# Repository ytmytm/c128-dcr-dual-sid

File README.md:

# Dual SID for C128DCR and C128D

This is a daughterboard that allows to have dual SID audio in a C128DCR. Although C128DCR has a huge case the space near SID and MMU is very awkward due to power supply.

This project is meant for two 8580 chips, as far as I know the only type installed in C128DCRs. But you never know, so just in case I left information about supporting 6581 SIDs too.

## Background

The goal of this project was to make the PCB fit in the narrow area between power supply and already installed
[256K MMU expansion](https://github.com/ytmytm/c128-mmu-256k-exp).

The audio output is mixed as 6-voices mono and passed through onboard amplifier to audio/video port.

The board supports various modes for external input, including noise reduction and digi boost.

## Design

This is basically a fusion of ideas from two projects:

- [C64 Stereo SID](https://github.com/tebl/C64-Stereo-SID) by tebl (seed project for schematic and PCB)
- [MixSID](http://henning-liebenau.de/mixsid/) by Henning Bekel (noise reduction and digi boost)

I have mostly done measurements and shaped the PCB.

### Schematic

PDF plot of [the schematic can be found here](kicad/plots/C128DCR%20Dual%20SID.pdf).

[kicad](kicad/) folder contains all the KiCad 6.0 project files for C128DCR.

[kicad-c128d](kicad-c128d/) folder contains all the KiCad 6.0 project files for C128D.

### PCB

[kicad/plots](kicad/plots) folder contains Gerber files for manufacturing a PCB.

The PCB hugs 256K MMU expansion board on one side, tries to avoid power supply on the other side and also has to leave space for screw standoff under the power supply module.

[kicad-c128d/plots](kicad-c128d/plots) folder contains all the KiCad 6.0 project files for C128D.

## PCB Assembly

Both SID chips must be identical. For C128DCR these should be usually MOS 8580 powered by 9V.

For 8580:

- be sure that the voltage between pins 14 (GND) and 28 (VDD) of SID socket is 9V
- do not install resistor R8
- use 22nF (symbol 223) capacitors for C71/C72

For 6581:

- be sure that the voltage between pins 14 (GND) and 28 (VDD) of SID socket is 12V
- install resistor R8
- use 470pF (symbol 471) capacitors for C71/C72

## Jumpers

Jumpers JP1/JP3 (SID#1) and JP2/JP4 (SID#2) control external input/noise reduction/digi boost signal routing.

JP1 and JP2 (square pad is pin 1):

- short 1-2 for noise reduction
- short 2-3 to pass external input from audio/video port

JP3 and JP4 (square pad is pin 1):

- short 1-2 to choose signal selected by JP1/JP2: external input or noise reduction
- short 2-3 to enable digi boost instead, this is meant for 8580

You can also keep all jumpers open to make external input floating. Some people claim that it's another way of reducing the noise.

For digi boost additionally set RV1 and RV2 trimmers while playing some sampled audio to bring digital sound to an acceptable volume level relative to regular SID voices.

[MixSID configuration tool](http://henning-liebenau.de/mixsid/configurator.html) has excellent description of both noise reduction and digi boost modes.

On the image above there is a single ARMSID as primary SID and an unpopulated socket for secondary SID.

For both chips the board is configured with JP3/JP4 for digi boost, so JP1/JP2 set to noise reduction are irrelevant.

Note that R8 is installed here by mistake, but its one leg was cut.

## Installation tips

### C128DCR

- solder round pins to two rows of the `SID_ADAPTER` footprint first.
- then solder lowest components first: the resistors (skip R8 if you are going to use 8580 chips)
- then two sockets for primary and secondary SIDs, check the orientation
- finally capacitors and trimmers; pay attention to the correct C70/C71 values

There are small holes in the PCB where plastic standoffs can be put to support the board on both ends and reduce stress on the mainboard SID socket.
It's especially important on the top right end, next to secondary SID.

After assembling two such boards I noticed that power supply modules in different C128DCRs have different dimensions.
To be sure that nothing will be shorted I put kapton tape on the whole left-hand side of the board after installation, also covering socketed primary SID.

### C128D

Start by soldering round pins to row closest to the PCB's edge and to the row marked on the silkscreen. Then proceed with C128DCR instructions.

## SID#2 chip select signal and testing

You need to decide where in the I/O memory space SID#2 will be available.
Even though signal for $D700 is easily available on C128 (it's pin 12 of U3) most stereo/dual SID tunes use $D420, $D500 or $DE00.

For quick tests SID#2 chip select signal (`/CS2_IN`, the square pad on J4 connector) can come from `I/O1` signal to make SID#2 appear at $DE00 address.
You don't need to reach to expansion port for that, it's already available on pin 9 of U3. Obviously it's not compatible with cartridges but allows for a quick test.

Download this tune: https://csdb.dk/release/?id=96893 and run. Hit '3' to choose $DE00 and you should hear the music - it starts immediately playing on SID#2 channels, SID#1 joins later - after about 30s.

Check out [my other project](https://github.com/ytmytm/c128-u3-replacement) for a better solution to make SID#2 appear at $D420, $D500 (in C64 mode) and optionally at $DE00.

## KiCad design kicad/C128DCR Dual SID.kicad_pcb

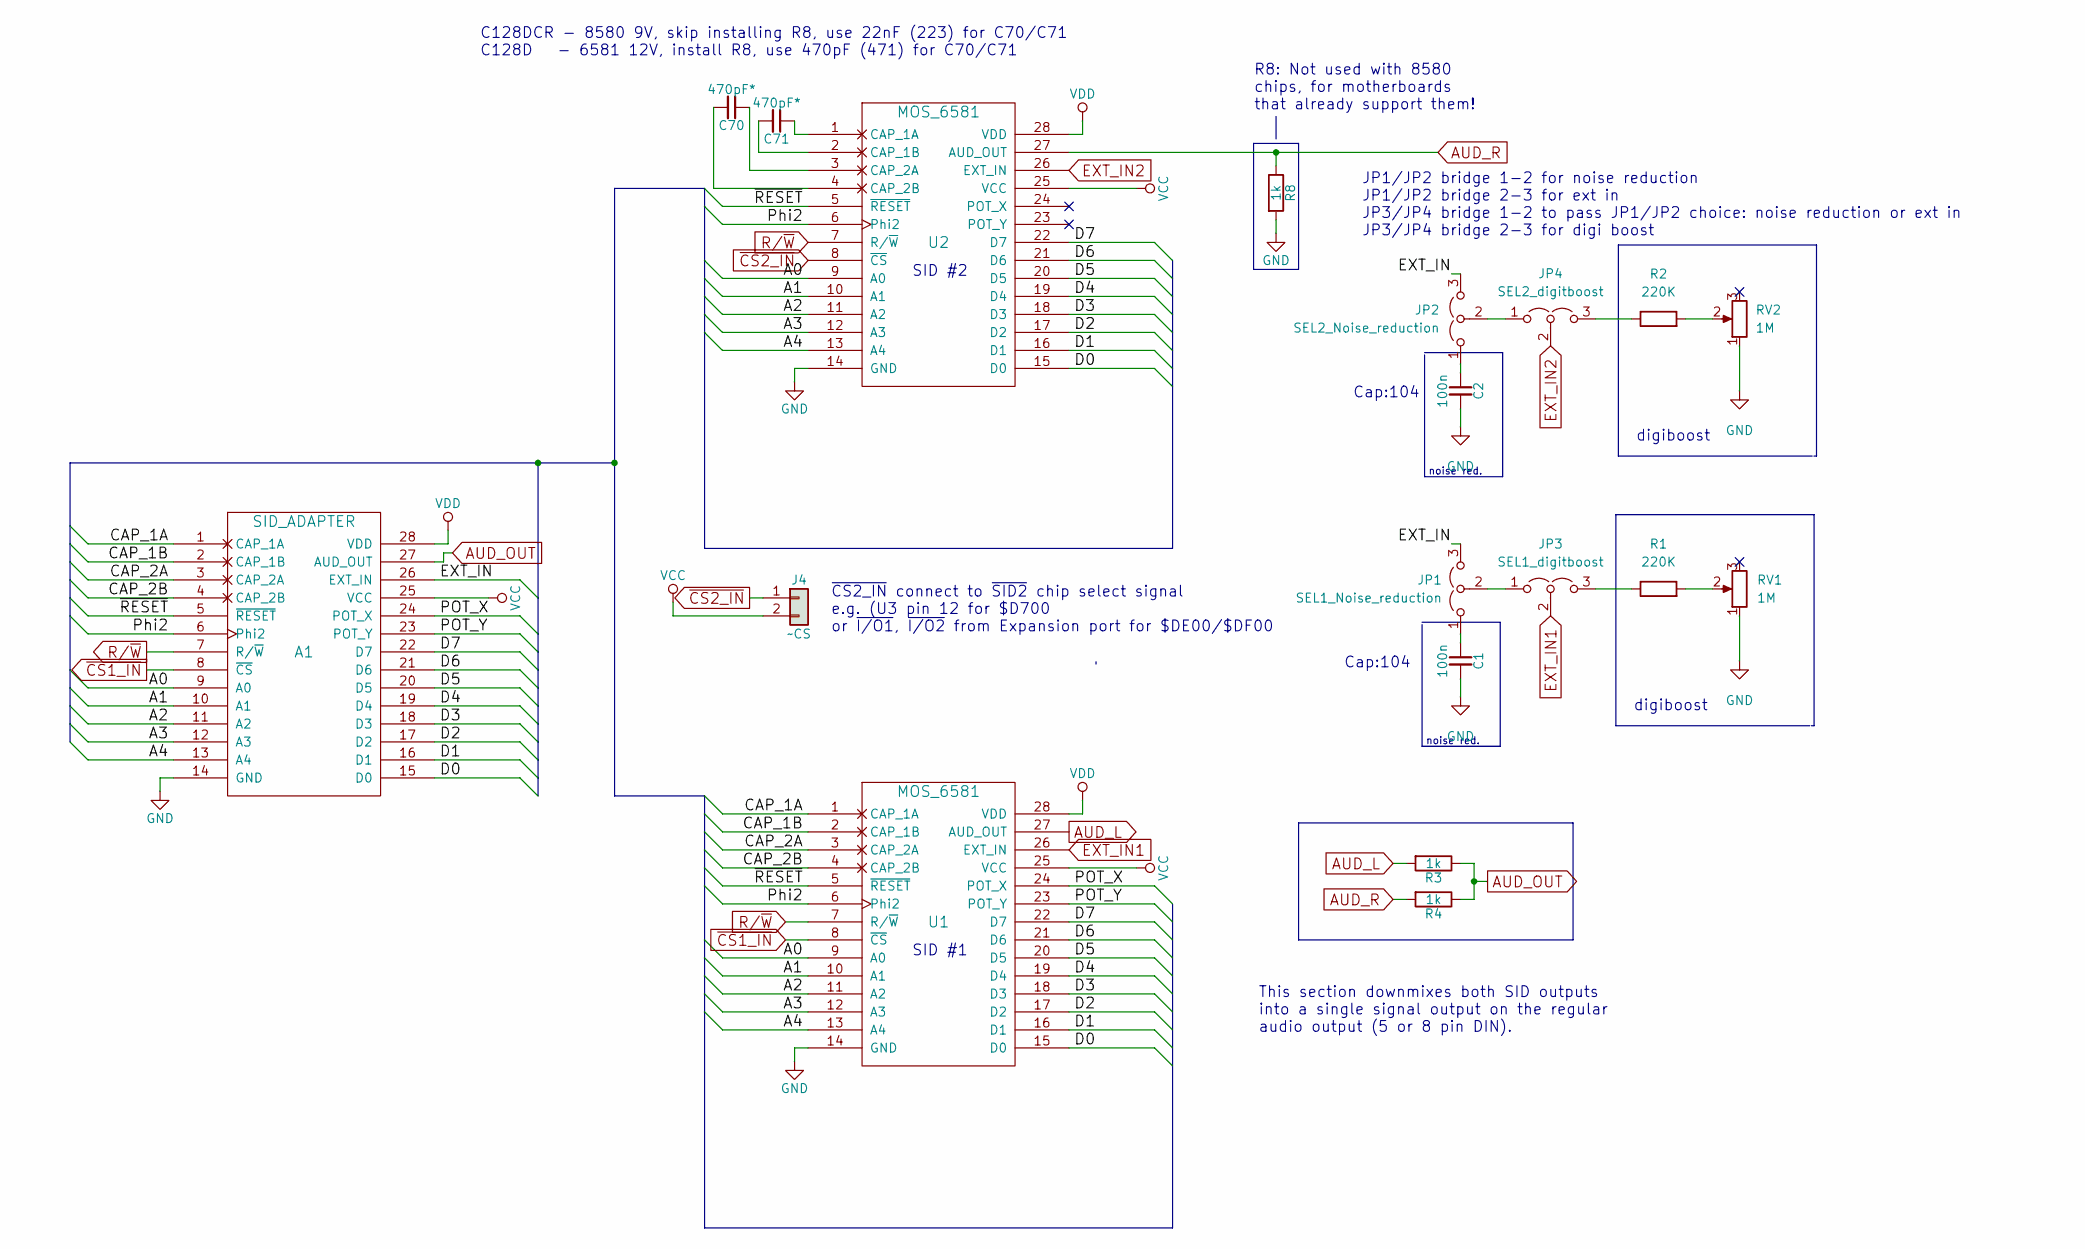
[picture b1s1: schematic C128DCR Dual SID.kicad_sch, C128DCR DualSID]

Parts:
A1: SID_ADAPTER; MOS_6581_Adapter
C1, C2: 100n; C_Disc_D4.7mm_W2.5mm_P5.00mm
C70, C71: 470pF*; C_Disc_D4.7mm_W2.5mm_P5.00mm
J4: ~CS; Pin_Header_Straight_1x02_Pitch2.54mm
JP1: SEL1_Noise_reduction; PinHeader_1x03_P2.54mm_Vertical
JP2: SEL2_Noise_reduction; PinHeader_1x03_P2.54mm_Vertical
JP3: SEL1_digitboost; PinHeader_1x03_P2.54mm_Vertical
JP4: SEL2_digitboost; PinHeader_1x03_P2.54mm_Vertical
R1, R2: 220K; R_Axial_DIN0207_L6.3mm_D2.5mm_P10.16mm_Horizontal
R3, R4, R8: 1k; R_Axial_DIN0207_L6.3mm_D2.5mm_P10.16mm_Horizontal
RV1, RV2: 1M; Potentiometer_Piher_PT-10-V05_Vertical
U1, U2: MOS_6581; DIP-28_W15.24mm_Socket

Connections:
/A0: A1.9 (A0), U1.9 (A0), U2.9 (A0)
/A1: A1.10 (A1), U1.10 (A1), U2.10 (A1)
/A2: A1.11 (A2), U1.11 (A2), U2.11 (A2)
/A3: A1.12 (A3), U1.12 (A3), U2.12 (A3)
/A4: A1.13 (A4), U1.13 (A4), U2.13 (A4)
/CAP_1A: A1.1 (CAP_1A), U1.1 (CAP_1A)
/CAP_1B: A1.2 (CAP_1B), U1.2 (CAP_1B)
/CAP_2A: A1.3 (CAP_2A), U1.3 (CAP_2A)
/CAP_2B: A1.4 (CAP_2B), U1.4 (CAP_2B)
/D0: A1.15 (D0), U1.15 (D0), U2.15 (D0)
/D1: A1.16 (D1), U1.16 (D1), U2.16 (D1)
/D2: A1.17 (D2), U1.17 (D2), U2.17 (D2)
/D3: A1.18 (D3), U1.18 (D3), U2.18 (D3)
/D4: A1.19 (D4), U1.19 (D4), U2.19 (D4)
/D5: A1.20 (D5), U1.20 (D5), U2.20 (D5)
/D6: A1.21 (D6), U1.21 (D6), U2.21 (D6)
/D7: A1.22 (D7), U1.22 (D7), U2.22 (D7)
/EXT_IN: A1.26 (EXT_IN), JP1.3 (B), JP2.3 (B)
/POT_X: A1.24 (POT_X), U1.24 (POT_X)
/POT_Y: A1.23 (POT_Y), U1.23 (POT_Y)
/Phi2: A1.6 (Phi2), U1.6 (Phi2), U2.6 (Phi2)
/~RESET: A1.5 (~RESET), U1.5 (~RESET), U2.5 (~RESET)
AUD_L: R3.2, U1.27 (AUD_OUT)
AUD_OUT: A1.27 (AUD_OUT), R3.1, R4.1
AUD_R: R4.2, R8.1, U2.27 (AUD_OUT)
EXT_IN1: JP3.2 (C), U1.26 (EXT_IN)
EXT_IN2: JP4.2 (C), U2.26 (EXT_IN)
GND: A1.14 (GND), C1.2, C2.2, R8.2, RV1.1, RV2.1, U1.14 (GND), U2.14 (GND)
unnamed: C1.1, JP1.1 (A)
unnamed: C70.1, U2.3 (CAP_2A)
unnamed: C70.2, U2.4 (CAP_2B)
unnamed: C71.1, U2.1 (CAP_1A)
unnamed: C71.2, U2.2 (CAP_1B)
unnamed: C2.1, JP2.1 (A)
unnamed: JP2.2 (C), JP4.1 (A)
unnamed: JP1.2 (C), JP3.1 (A)
unnamed: JP4.3 (B), R2.1
unnamed: JP3.3 (B), R1.1
unnamed: R1.2, RV1.2
unnamed: R2.2, RV2.2
R/~W: A1.7 (R/~W), U1.7 (R/~W), U2.7 (R/~W)
VCC: A1.25 (VCC), J4.2, U1.25 (VCC), U2.25 (VCC)
VDD: A1.28 (VDD), U1.28 (VDD), U2.28 (VDD)
~CS1_IN: A1.8 (~CS), U1.8 (~CS)
~CS2_IN: J4.1, U2.8 (~CS)

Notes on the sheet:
~{CS2_IN} connect to ~{SID2} chip select signal e.g. (U3 pin 12 for $D700 or ~{I/O1}, ~{I/O2} from Expansion port for $DE00/$DF00
SID #2
Cap:104
digiboost
noise red.
JP1/JP2 bridge 1-2 for noise reduction JP1/JP2 bridge 2-3 for ext in JP3/JP4 bridge 1-2 to pass JP1/JP2 choice: noise reduction or ext in JP3/JP4 bridge 2-3 for digi boost
SID #1
This section downmixes both SID outputs into a single signal output on the regular audio output (5 or 8 pin DIN).
C128DCR - 8580 9V, skip installing R8, use 22nF (223) for C70/C71 C128D - 6581 12V, install R8, use 470pF (471) for C70/C71
R8: Not used with 8580 chips, for motherboards that already support them!

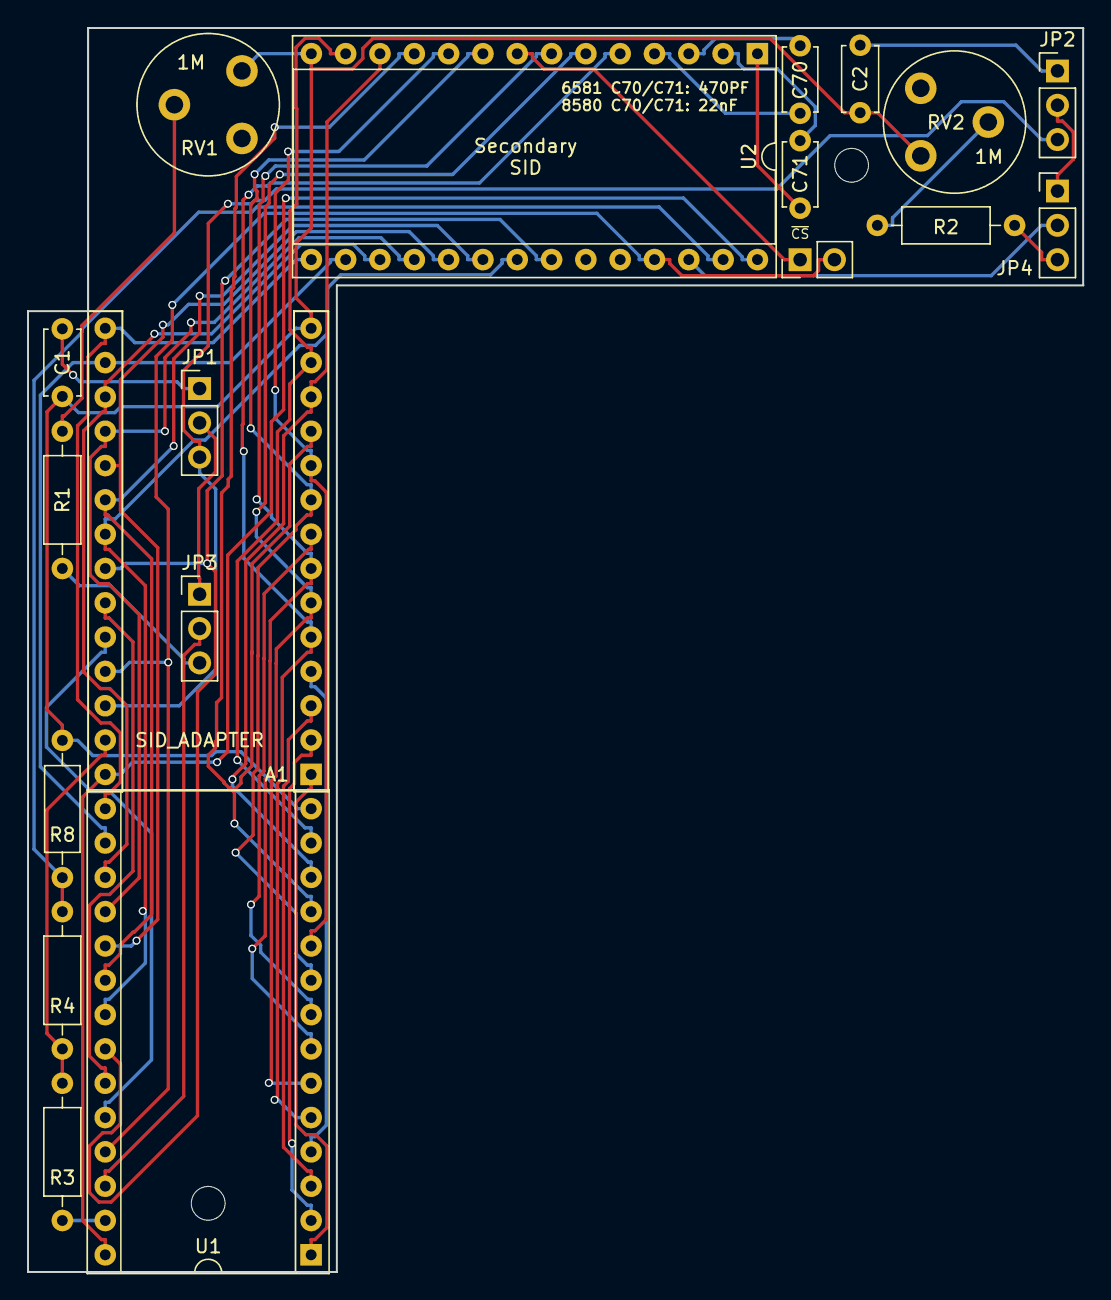
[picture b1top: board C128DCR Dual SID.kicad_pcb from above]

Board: 2 copper layers, 78.1 x 92.1 mm, 21 parts (0 on the bottom side), 45 nets.

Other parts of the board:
REF1, REF2: MountingHole_2.5mm

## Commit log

2023-01-02 typos
2023-01-03 photos
2023-10-24 PCB version that should fit in a C128D
2023-11-13 plot values on silkscreen in generated gerber files
2023-11-13 more info about C128D
2023-11-13 ignored files
